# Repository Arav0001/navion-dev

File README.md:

# NAVION - navion-dev
NAVION is a thrust-vector-controlled rocket accompanied by a custom two-board flight computer I designed, built, and flew.

## Results
NAVION's maiden flight reached a ~47 m apogee. The active TVC control loop tracked pitch & yaw through boost and was able to correct 4.5° of yaw error before losing control due to overwhelming pitch error and low motor power, after which the vehicle coasted and descended under parachute to a detected touchdown.
 
### Flight profile
Altitude, vertical velocity, and vertical acceleration across boost, descent, and touchdown, reconstructed from onboard sensor data, see [maiden flight data](FlightData/NAVION-1_DATA.csv):

### TVC response
Tracked gimbal deflection (X/Y) for pitch & yaw during the boost phase, up to TVC lockout at burnout:

## Hardware
 
### Flight computer
Two-board avionics stack: an STM32F4 control board and STM32F2 navigation board communicating over UART DMA, carrying a 9-axis IMU, barometer, GNSS receiver, SPI flash, and µSD storage.

### TVC gimbal
3D-printed 2-axis gimbal actuating the solid rocket motor with ±5° of pitch/yaw deflection, driven by two digital servos:

## Test footage
*TVC gimbal actuating in response to real-time orientation changes of the flight computer*
<video src="https://github.com/user-attachments/assets/a1468e4f-2fa1-48d4-a81f-83034c1c49a3" controls></video>

*Ground test of the black-powder parachute ejection system.*
<video src="https://github.com/user-attachments/assets/dc627b79-1247-45d9-82b1-cf85502bb5d8" controls></video>

## What's in this repo
- [`Code/`](https://github.com/Arav0001/navion-dev/tree/main/Code) - All the firmware for the flight computer.
    - [`CNTRL/`](https://github.com/Arav0001/navion-dev/tree/main/Code/CNTRL) - Firmware for the control (CNTRL) board, targeting the STM32F405RG (STM32CubeIDE Project).
	- [`NAVIG/`](https://github.com/Arav0001/navion-dev/tree/main/Code/NAVIG) - Firmware for the navigation (NAVIG) board, targeting the STM32F205RG (STM32CubeIDE Project).
	- [`CNTRL ESP32/`](https://github.com/Arav0001/navion-dev/tree/main/Code/CNTRL%20ESP32) - Firmware for the [Adafruit HUZZAH32 ESP32](https://www.adafruit.com/product/3405) that runs a webserver for launch control (PlatformIO Project). Contains launch control webserver assets in `data/`.
	- [`NAVION Ground Control/`](https://github.com/Arav0001/navion-dev/tree/main/Code/NAVION%20Ground%20Control) - Firmware for WIP (Work in progress, not currently used or working) ground control radio running off a [Adafruit Feather RFM95W](https://www.adafruit.com/product/3178) (PlatformIO Project).
- [`Designs/`](https://github.com/Arav0001/navion-dev/tree/main/Designs) - OpenRocket designs and simulations for the rocket.
- [`Schematics/`](https://github.com/Arav0001/navion-dev/tree/main/Schematics) - KiCad schematics and PCB files for the flight computer boards.
- [`FlightData/`](https://github.com/Arav0001/navion-dev/tree/main/FlightData) - CSV flight data (only maiden flight as of now)

## Credits
- [FatFS](https://elm-chan.org/fsw/ff/) -> [driver I used](https://github.com/eziya/STM32_SPI_SDCARD)
- [lbthomsen’s W25QXX Driver](https://github.com/lbthomsen/stm32-w25qxx)
- [Sebastian Magdwick’s AHRS Filter](https://x-io.co.uk/open-source-imu-and-ahrs-algorithms/)
- [Adafruit BMP390 Calibration Routine](https://github.com/adafruit/Adafruit_BMP3XX)
- [Chart.js](https://github.com/chartjs/Chart.js)

## Acknowledgements
Thank you to Cory Russell and Merrick Ryman at Birket Engineering for providing guidance and teaching me the skills I needed to make this project happen!

## Inspiration
This project drew inspiration from [Joe Barnard's Scout rocket](https://youtu.be/SH3lR2GLgT0) over at [BPS.space](https://BPS.space). Go check him out!

## Contact
Feel free to contact me at <arav.sonawane@gatech.edu>

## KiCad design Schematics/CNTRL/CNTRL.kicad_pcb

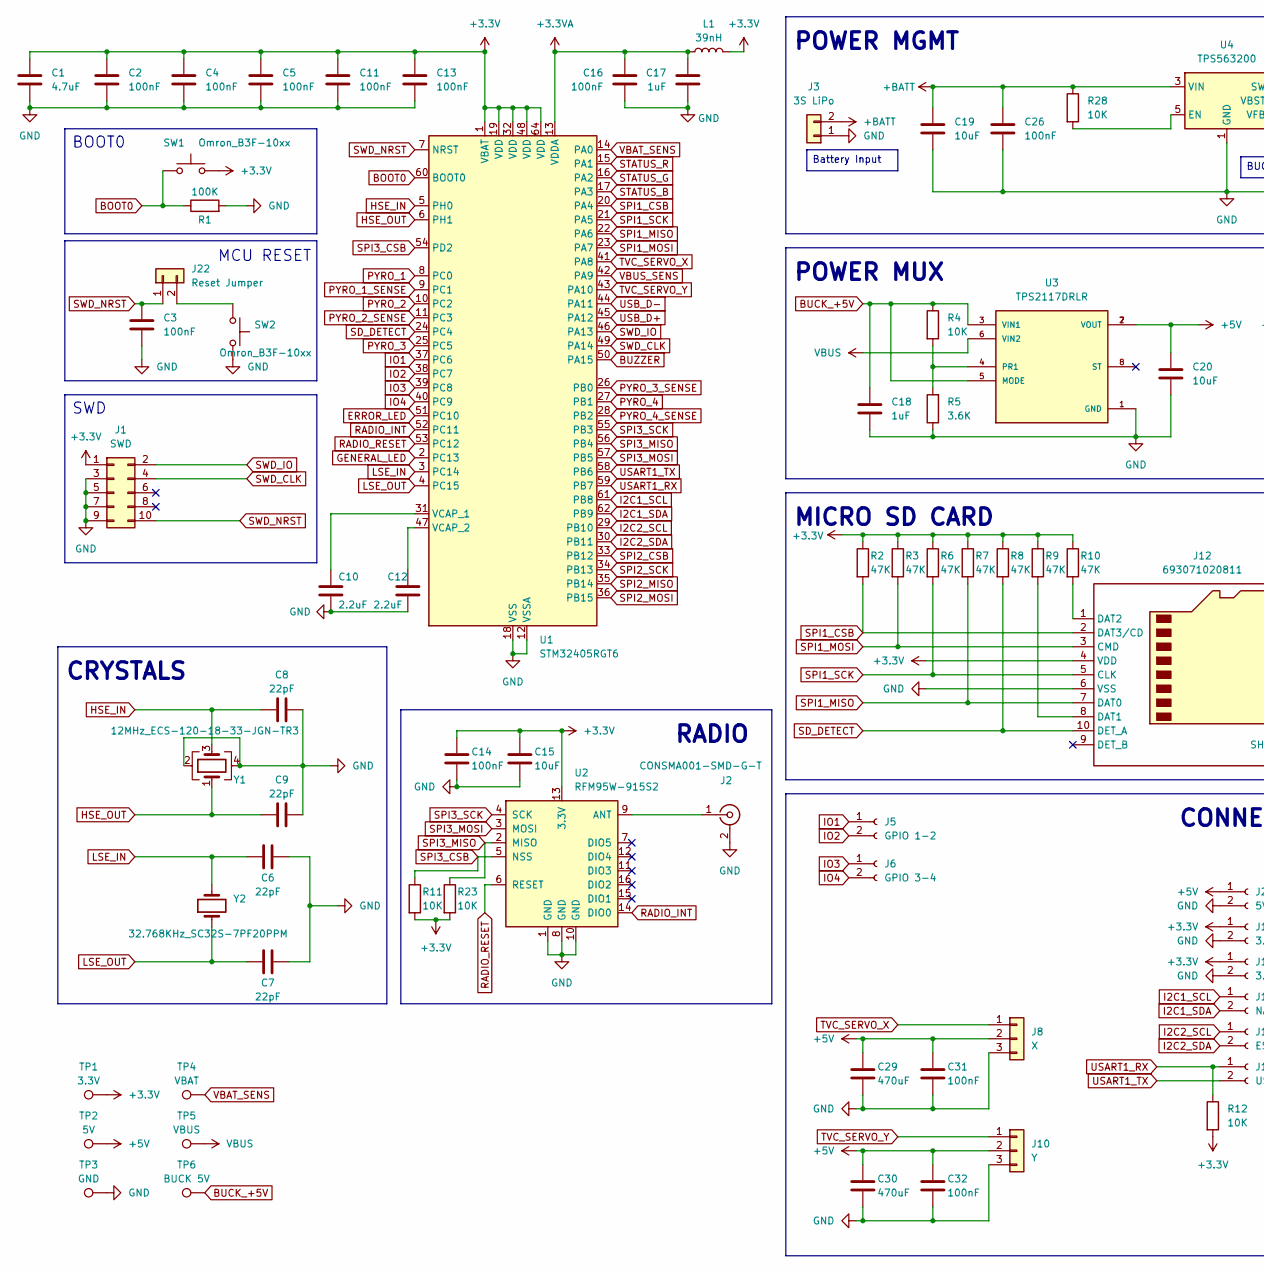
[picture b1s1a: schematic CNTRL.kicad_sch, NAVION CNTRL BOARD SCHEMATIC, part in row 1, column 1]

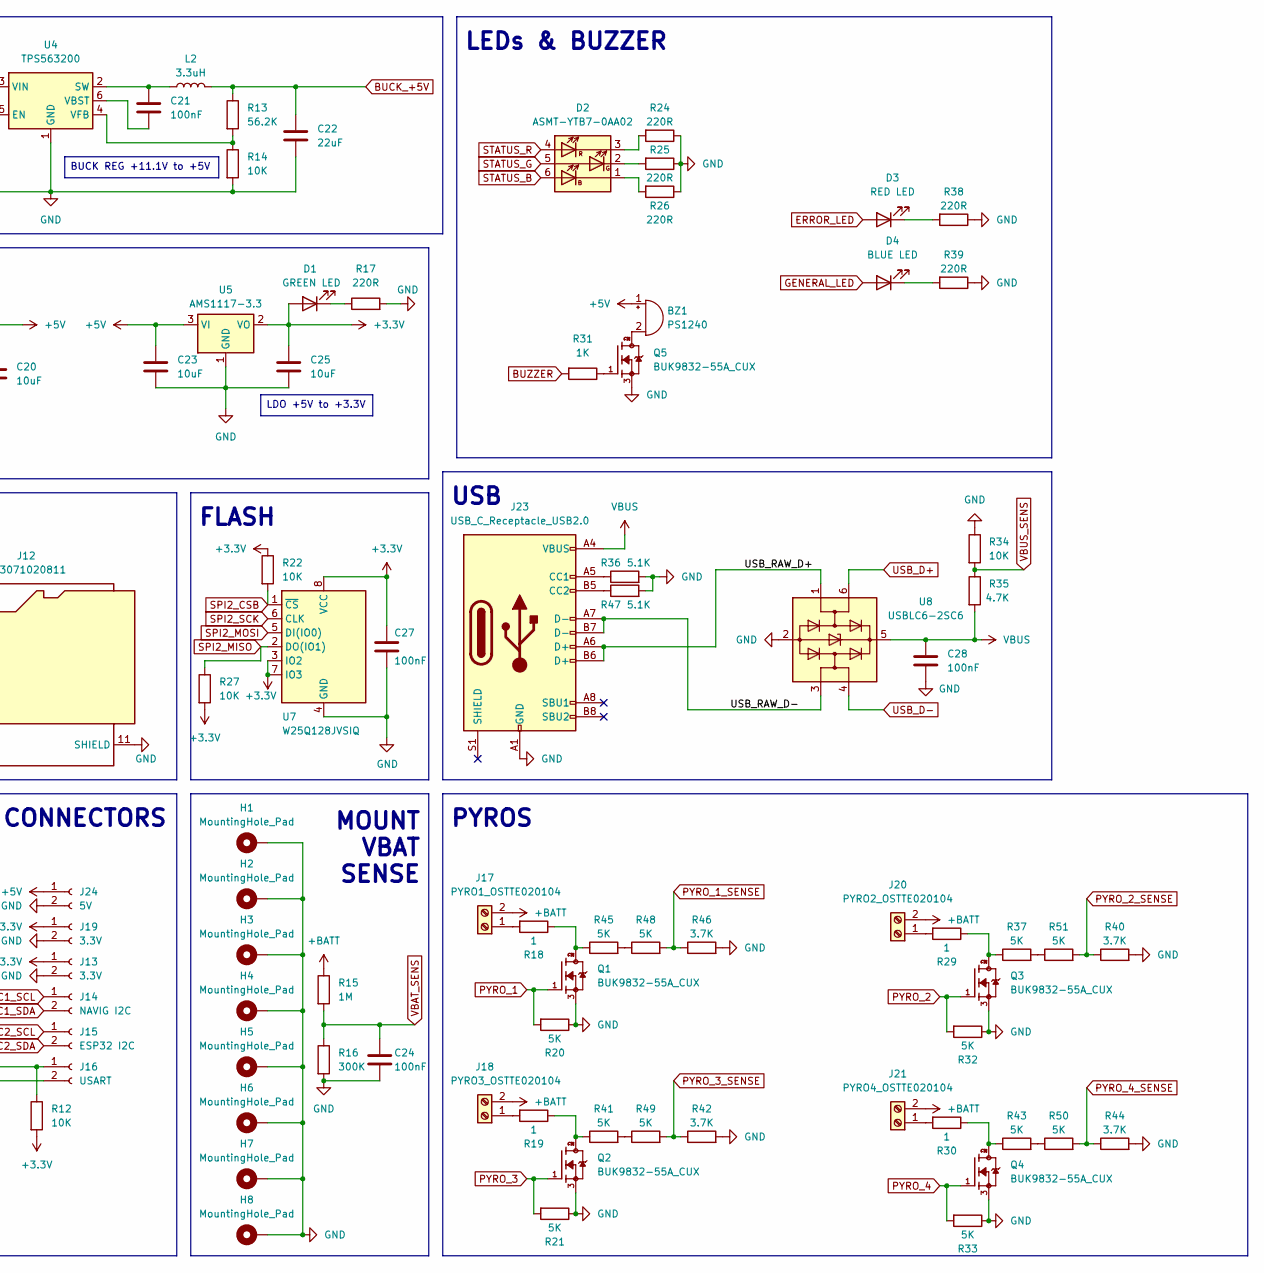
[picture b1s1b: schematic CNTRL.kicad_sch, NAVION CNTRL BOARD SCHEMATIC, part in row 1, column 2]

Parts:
BZ1: PS1240; Buzzer_TDK_PS1240P02BT_D12.2mm_H6.5mm
C1: 4.7uF; C_0603_1608Metric
C2, C3, C4, C5, C11, C13, C14, C16, C21, C24, C26, C27, C28, C31, C32: 100nF; C_0603_1608Metric
C6, C7, C8, C9: 22pF; C_0603_1608Metric
C10, C12: 2.2uF; C_0603_1608Metric
C15, C19, C20, C23, C25: 10uF; C_0603_1608Metric
C17, C18: 1uF; C_0603_1608Metric
C22: 22uF; C_0603_1608Metric
C29, C30: 470uF; CP_Radial_D6.3mm_P2.50mm
D1: GREEN LED; LED_0603_1608Metric
D2: ASMT-YTB7-0AA02; LED_Avago_PLCC6_3x2.8mm
D3: RED LED; LED_0603_1608Metric
D4: BLUE LED; LED_0603_1608Metric
H1, H2, H3, H4, H5, H6, H7, H8: MountingHole_Pad; MountingHole_2.2mm_M2_Pad_TopBottom
J1: SWD; PinHeader_2x05_P1.27mm_Vertical_SMD
J2: CONSMA001-SMD-G-T; LINX_CONSMA001-SMD-G-T
J3: 3S LiPo; AMASS_XT30UPB-M_1x02_P5.0mm_Vertical
J5: GPIO 1-2; TerminalBlock_Phoenix_MPT-0,5-2-2.54_1x02_P2.54mm_Horizontal
J6: GPIO 3-4; TerminalBlock_Phoenix_MPT-0,5-2-2.54_1x02_P2.54mm_Horizontal
J8: X; TerminalBlock_Phoenix_MPT-0,5-3-2.54_1x03_P2.54mm_Horizontal
J10: Y; TerminalBlock_Phoenix_MPT-0,5-3-2.54_1x03_P2.54mm_Horizontal
J12: 693071020811
J13, J19: 3.3V; JST_XH_B2B-XH-A_1x02_P2.50mm_Vertical
J14: NAVIG I2C; JST_XH_B2B-XH-A_1x02_P2.50mm_Vertical
J15: ESP32 I2C; JST_XH_B2B-XH-A_1x02_P2.50mm_Vertical
J16: USART; JST_XH_B2B-XH-A_1x02_P2.50mm_Vertical
J17: PYRO1_OSTTE020104; TerminalBlock_4Ucon_1x02_P3.50mm_Vertical
J18: PYRO3_OSTTE020104; TerminalBlock_4Ucon_1x02_P3.50mm_Vertical
J20: PYRO2_OSTTE020104; TerminalBlock_4Ucon_1x02_P3.50mm_Vertical
J21: PYRO4_OSTTE020104; TerminalBlock_4Ucon_1x02_P3.50mm_Vertical
J22: Reset Jumper; PinHeader_1x02_P2.54mm_Vertical
J23: USB_C_Receptacle_USB2.0; USB_C_Receptacle_GCT_USB4105-xx-A_16P_TopMnt_Horizontal
J24: 5V; JST_XH_B2B-XH-A_1x02_P2.50mm_Vertical
L1: 39nH; L_0603_1608Metric
L2: 3.3uH; L_1210_3225Metric_Pad1.42x2.65mm_HandSolder
Q1, Q2, Q3, Q4, Q5: BUK9832-55A_CUX; TRANS_BUK9832-55A_CUX; PARTREV 02
R1: 100K; R_0603_1608Metric
R2, R3, R6, R7, R8, R9, R10: 47K; R_0603_1608Metric
R4, R11, R12, R14, R22, R23, R27, R28, R34: 10K; R_0603_1608Metric
R5: 3.6K; R_0603_1608Metric
R13: 56.2K; R_0603_1608Metric
R15: 1M; R_0603_1608Metric
R16: 300K; R_0603_1608Metric
R17, R24, R25, R26, R38, R39: 220R; R_0603_1608Metric
R18, R19, R29, R30: 1; R_0603_1608Metric
R20, R21, R32, R33, R37, R41, R43, R45, R48, R49, R50, R51: 5K; R_0603_1608Metric
R31: 1K; R_0603_1608Metric
R35: 4.7K; R_0603_1608Metric
R36, R47: 5.1K; R_0603_1608Metric
R40, R42, R44, R46: 3.7K; R_0603_1608Metric
SW1, SW2: Omron_B3F-10xx; SW_TH_Tactile_Omron_B3F-10xx
TP1: 3.3V; TestPoint_Pad_D2.0mm
TP2: 5V; TestPoint_Pad_D2.0mm
TP3: GND; TestPoint_Pad_D2.0mm
TP4: VBAT; TestPoint_Pad_D2.0mm
TP5: VBUS; TestPoint_Pad_D2.0mm
TP6: BUCK 5V; TestPoint_Pad_D2.0mm
U1: STM32405RGT6; LQFP-64_10x10mm_P0.5mm
U2: RFM95W-915S2; HOPERF_RFM9XW_SMD
U3: TPS2117DRLR; SOT-583-8; PARTREV A
U4: TPS563200; SOT-23-6
U5: AMS1117-3.3; SOT-223-3_TabPin2
U7: W25Q128JVSIQ; SOIC-8_5.3x5.3mm_P1.27mm
U8: USBLC6-2SC6; SOT-23-6
Y1: 12MHz_ECS-120-18-33-JGN-TR3; Crystal_SMD_3225-4Pin_3.2x2.5mm
Y2: 32.768KHz_SC32S-7PF20PPM; Crystal_SMD_3215-2Pin_3.2x1.5mm

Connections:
+3.3V: C1.1, C2.1, C4.1, C5.1, C11.1, C13.1, C14.2, C15.2, C25.1, C27.1, D1.2 (A), J1.1, J12.4 (VDD), J13.1, J19.1, L1.1, R2.1, R3.1, R6.1, R7.1, R8.1, R9.1, R10.1, R11.2, R12.2, R22.1, R23.2, R27.2, SW1.2, TP1.1, U1.1 (VBAT), U1.19 (VDD), U1.32 (VDD), U1.48 (VDD), U1.64 (VDD), U2.13 (3.3V), U5.2 (VO), U7.3 (IO2), U7.7 (IO3), U7.8 (VCC)
+3.3VA: C16.1, C17.1, L1.2, U1.13 (VDDA)
+5V: BZ1.1 (-), C20.1, C23.1, C29.2, C30.2, C31.2, C32.2, J8.2, J10.2, J24.1, TP2.1, U3.2 (VOUT), U3.7 (VOUT), U5.3 (VI)
+BATT: C19.1, C26.1, J3.2, J17.2, J18.2, J20.2, J21.2, R15.1, R28.1, U4.3 (VIN)
/USB_RAW_D+: J23.A6 (D+), J23.B6 (D+), U8.1 (I/O1)
/USB_RAW_D-: J23.A7 (D-), J23.B7 (D-), U8.3 (I/O2)
BOOT0: R1.1, SW1.1, U1.60 (BOOT0)
BUCK_+5V: C18.1, C22.1, L2.2, R4.1, R13.1, TP6.1, U3.3 (VIN1), U3.5 (MODE)
BUZZER: R31.2, U1.50 (PA15)
ERROR_LED: D3.2 (A), U1.51 (PC10)
GENERAL_LED: D4.2 (A), U1.2 (PC13)
GND: C1.2, C2.2, C3.2, C4.2, C5.2, C6.2, C7.2, C8.1, C9.2, C10.1, C11.2, C12.1, C13.2, C14.1, C15.1, C16.2, C17.2, C18.2, C19.2, C20.2, C22.2, C23.2, C24.1, C25.2, C26.2, C27.2, C28.2, C29.1, C30.1, C31.1, C32.1, H1.1, H2.1, H3.1, H4.1, H5.1, H6.1, H7.1, H8.1, J1.3, J1.5, J1.7, J1.9, J2.2 (Ext), J3.1, J8.3, J10.3, J12.6 (VSS), J12.11 (SHIELD), J13.2, J19.2, J23.A1 (GND), J23.A12 (GND), J23.B1 (GND), J23.B12 (GND), J24.2, Q1.3, Q2.3, Q3.3, Q4.3, Q5.3, R1.2, R5.1, R14.2, R16.2, R17.2, R20.1, R21.1, R24.1, R25.1, R26.1, R32.1, R33.1, R34.1, R36.2, R38.1, R39.1, R40.2, R42.2, R44.2, R46.2, R47.2, SW2.2, TP3.1, U1.12 (VSSA), U1.18 (VSS), U1.63 (VSS), U2.1 (GND), U2.8 (GND), U2.10 (GND), U3.1 (GND), U4.1 (GND), U5.1 (GND), U7.4 (GND), U8.2 (GND), Y1.2, Y1.4
HSE_IN: C8.2, U1.5 (PH0), Y1.3
HSE_OUT: C9.1, U1.6 (PH1), Y1.1
I2C1_SCL: J14.1, U1.61 (PB8)
I2C1_SDA: J14.2, U1.62 (PB9)
I2C2_SCL: J15.1, U1.29 (PB10)
I2C2_SDA: J15.2, U1.30 (PB11)
IO1: J5.1, U1.37 (PC6)
IO2: J5.2, U1.38 (PC7)
IO3: J6.1, U1.39 (PC8)
IO4: J6.2, U1.40 (PC9)
LSE_IN: C6.1, U1.3 (PC14), Y2.2
LSE_OUT: C7.1, U1.4 (PC15), Y2.1
unnamed: BZ1.2 (+), Q5.2, Q5.4
unnamed: D1.1 (K), R17.1
unnamed: D2.1 (KB), R26.2
unnamed: D2.2 (KG), R25.2
unnamed: D2.3 (KR), R24.2
unnamed: D3.1 (K), R38.2
unnamed: D4.1 (K), R39.2
unnamed: J2.1 (In), U2.9 (ANT)
unnamed: J12.8 (DAT1), R9.2
unnamed: J12.1 (DAT2), R10.2
unnamed: J17.1, R18.2
unnamed: J18.1, R19.2
unnamed: J20.1, R29.2
unnamed: J21.1, R30.2
unnamed: J22.2, SW2.1
unnamed: J23.A5 (CC1), R36.1
unnamed: J23.B5 (CC2), R47.1
unnamed: Q1.2, Q1.4, R18.1, R45.1
unnamed: Q2.2, Q2.4, R19.1, R41.1
unnamed: Q3.2, Q3.4, R29.1, R37.1
unnamed: Q4.2, Q4.4, R30.1, R43.1
unnamed: Q5.1, R31.1
unnamed: R37.2, R51.1
unnamed: R41.2, R49.1
unnamed: R43.2, R50.1
unnamed: R45.2, R48.1
unnamed: C10.2, U1.31 (VCAP_1)
unnamed: C12.2, U1.47 (VCAP_2)
unnamed: R4.2, R5.2, U3.4 (PR1)
unnamed: R28.2, U4.5 (EN)
unnamed: C21.1, L2.1, U4.2 (SW)
unnamed: C21.2, U4.6 (VBST)
unnamed: R13.2, R14.1, U4.4 (VFB)
PYRO_1: Q1.1, R20.2, U1.8 (PC0)
PYRO_1_SENSE: R46.1, R48.2, U1.9 (PC1)
PYRO_2: Q3.1, R32.2, U1.10 (PC2)
PYRO_2_SENSE: R40.1, R51.2, U1.11 (PC3)
PYRO_3: Q2.1, R21.2, U1.25 (PC5)
PYRO_3_SENSE: R42.1, R49.2, U1.26 (PB0)
PYRO_4: Q4.1, R33.2, U1.27 (PB1)
PYRO_4_SENSE: R44.1, R50.2, U1.28 (PB2)
RADIO_INT: U1.52 (PC11), U2.14 (DIO0)
RADIO_RESET: U1.53 (PC12), U2.6 (RESET)
SD_DETECT: J12.10 (DET_A), R8.2, U1.24 (PC4)
SPI1_CSB: J12.2 (DAT3/CD), R2.2, U1.20 (PA4)
SPI1_MISO: J12.7 (DAT0), R7.2, U1.22 (PA6)
SPI1_MOSI: J12.3 (CMD), R3.2, U1.23 (PA7)
SPI1_SCK: J12.5 (CLK), R6.2, U1.21 (PA5)
SPI2_CSB: R22.2, U1.33 (PB12), U7.1 (~CS)
SPI2_MISO: R27.1, U1.35 (PB14), U7.2 (DO(IO1))
SPI2_MOSI: U1.36 (PB15), U7.5 (DI(IO0))
SPI2_SCK: U1.34 (PB13), U7.6 (CLK)
SPI3_CSB: R11.1, U1.54 (PD2), U2.5 (NSS)
SPI3_MISO: R23.1, U1.56 (PB4), U2.2 (MISO)
SPI3_MOSI: U1.57 (PB5), U2.3 (MOSI)
SPI3_SCK: U1.55 (PB3), U2.4 (SCK)
STATUS_B: D2.6 (AB), U1.17 (PA3)
STATUS_G: D2.5 (AG), U1.16 (PA2)
STATUS_R: D2.4 (AR), U1.15 (PA1)
SWD_CLK: J1.4, U1.49 (PA14)
SWD_IO: J1.2, U1.46 (PA13)
SWD_NRST: C3.1, J1.10, J22.1, U1.7 (NRST)
TVC_SERVO_X: J8.1, U1.41 (PA8)
TVC_SERVO_Y: J10.1, U1.43 (PA10)
USART1_RX: J16.1, R12.1, U1.59 (PB7)
USART1_TX: J16.2, U1.58 (PB6)
USB_D+: U1.45 (PA12), U8.6 (I/O1)
USB_D-: U1.44 (PA11), U8.4 (I/O2)
VBAT_SENS: C24.2, R15.2, R16.1, TP4.1, U1.14 (PA0)
VBUS: C28.1, J23.A4 (VBUS), J23.A9 (VBUS), J23.B4 (VBUS), J23.B9 (VBUS), R35.2, TP5.1, U3.6 (VIN2), U8.5 (VBUS)
VBUS_SENS: R34.2, R35.1, U1.42 (PA9)

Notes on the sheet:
CONNECTORS
PYROS
BOOT0
POWER MUX
SWD
FLASH
LEDs & BUZZER
MCU RESET
MOUNT VBAT SENSE
CRYSTALS
MICRO SD CARD
POWER MGMT
RADIO
USB
Battery Input
LDO +5V to +3.3V
BUCK REG +11.1V to +5V

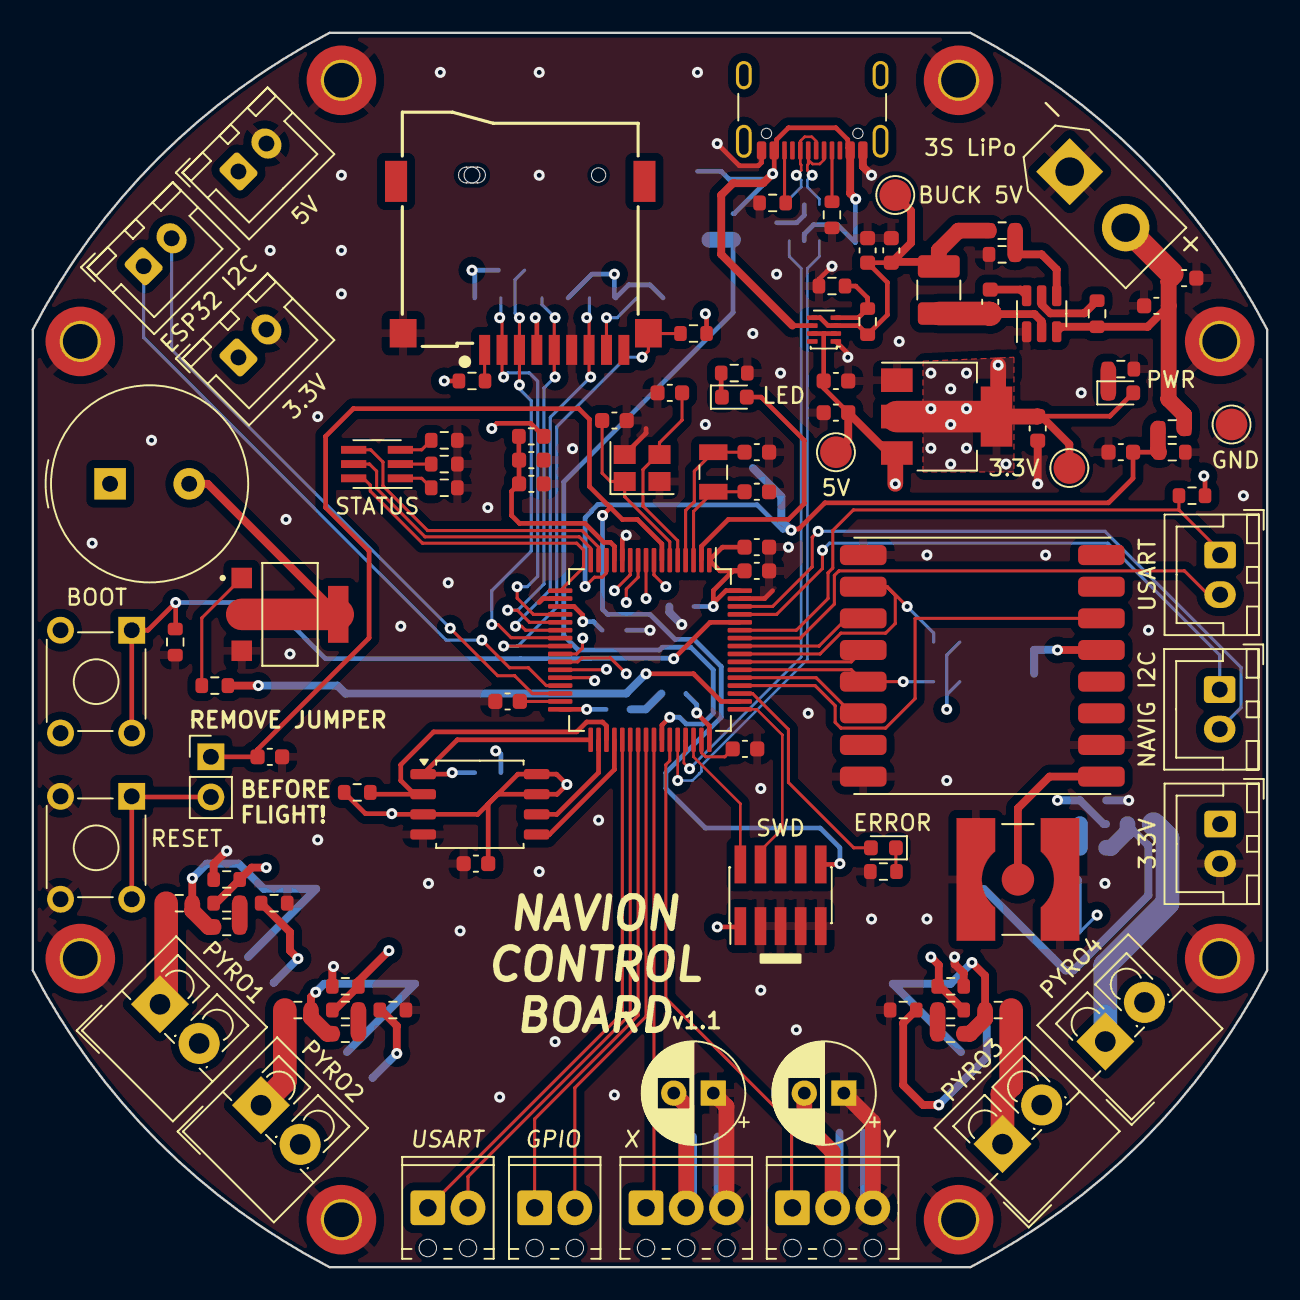
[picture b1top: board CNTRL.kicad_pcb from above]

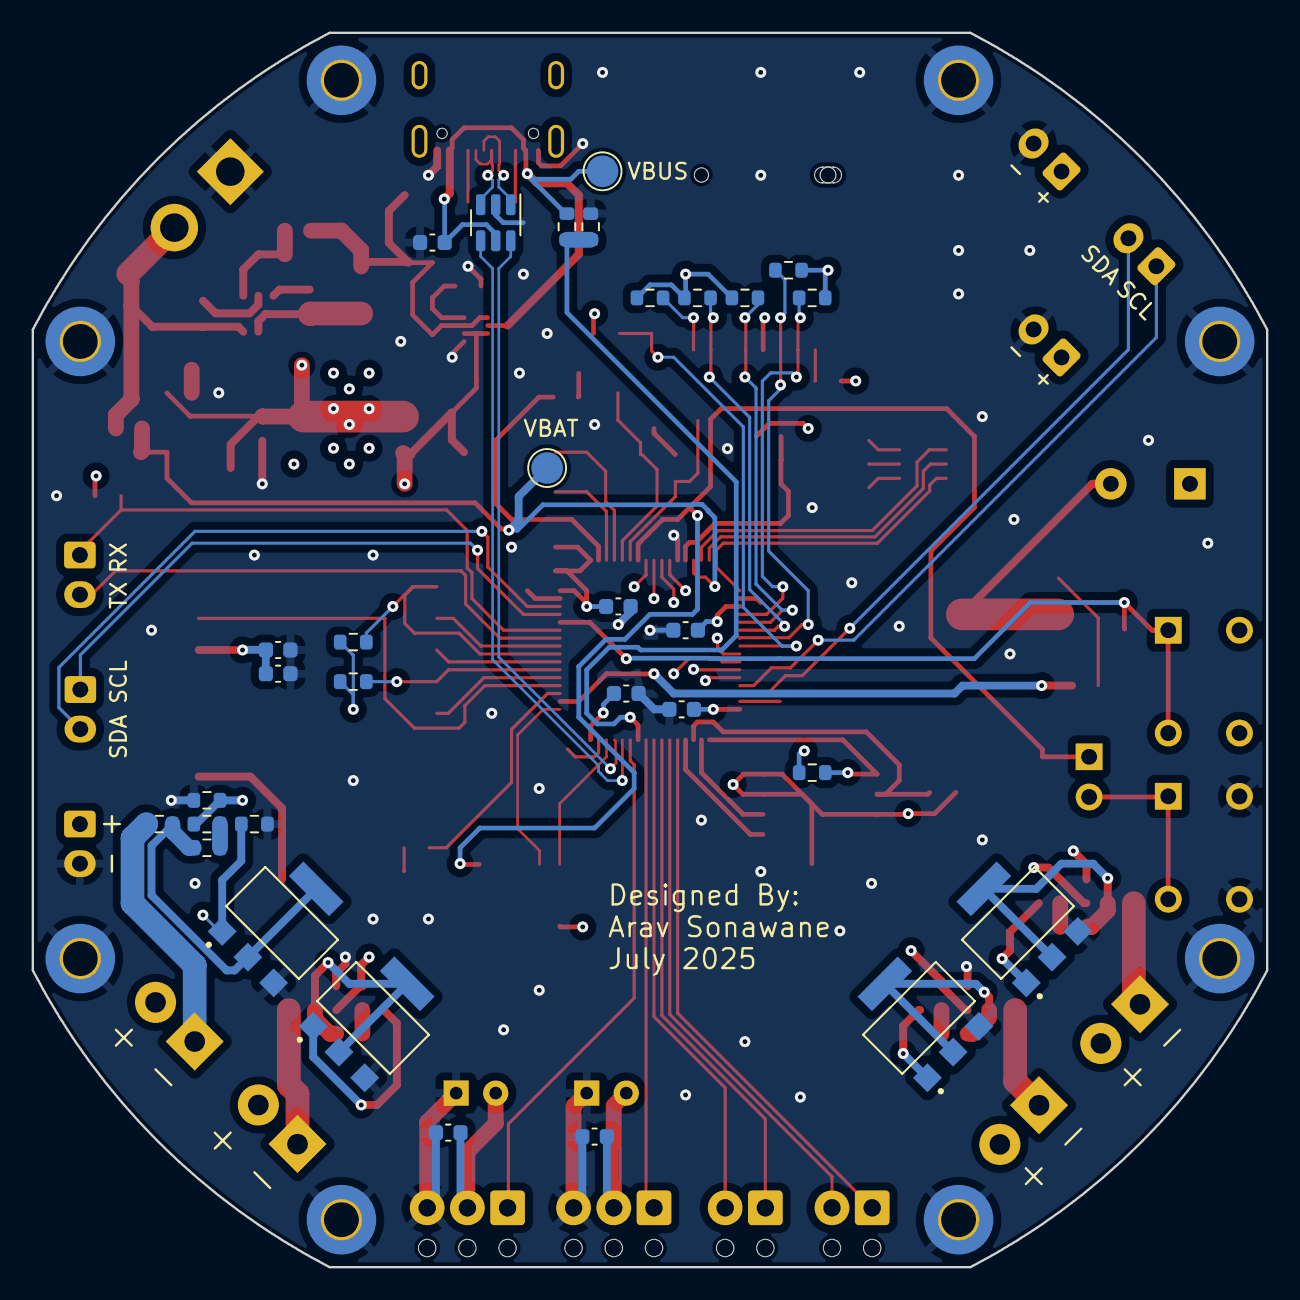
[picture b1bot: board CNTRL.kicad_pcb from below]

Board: 4 copper layers, 78.0 x 78.0 mm, 140 parts (31 on the bottom side), 95 nets.

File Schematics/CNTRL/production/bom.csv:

Designator,Footprint,Quantity,Value,LCSC Part #
BZ1,Buzzer_TDK_PS1240P02BT_D12.2mm_H6.5mm,1,PS1240,
C1,0603,1,4.7uF,
"C10, C12",0603,2,2.2uF,
"C11, C13, C14, C16, C2, C21, C24, C26, C27, C28, C3, C31, C32, C4, C5",0603,15,100nF,
"C15, C19, C20, C23, C25",0603,5,10uF,
"C17, C18",0603,2,1uF,
C22,0603,1,22uF,
"C29, C30",CP_Radial_D6.3mm_P2.50mm,2,470uF,
"C6, C7, C8, C9",0603,4,22pF,
D1,0603,1,GREEN LED,
D2,LED_Avago_PLCC6_3x2.8mm,1,ASMT-YTB7-0AA02,
D3,0603,1,RED LED,
D4,0603,1,BLUE LED,
"H1, H2, H3, H4, H5, H6, H7, H8",MountingHole_2.2mm_M2_Pad_TopBottom,8,MountingHole_Pad,
J1,PinHeader_2x05_P1.27mm_Vertical_SMD,1,SWD,
J10,"TerminalBlock_Phoenix_MPT-0,5-3-2.54_1x03_P2.54mm_Horizontal",1,Y,
J12,693071020811,1,693071020811,
"J13, J19",JST_XH_B2B-XH-A_1x02_P2.50mm_Vertical,2,3.3V,
J14,JST_XH_B2B-XH-A_1x02_P2.50mm_Vertical,1,NAVIG I2C,
J15,JST_XH_B2B-XH-A_1x02_P2.50mm_Vertical,1,ESP32 I2C,
J16,JST_XH_B2B-XH-A_1x02_P2.50mm_Vertical,1,USART,
J17,TerminalBlock_4Ucon_1x02_P3.50mm_Vertical,1,PYRO1_OSTTE020104,
J18,TerminalBlock_4Ucon_1x02_P3.50mm_Vertical,1,PYRO3_OSTTE020104,
J2,LINX_CONSMA001-SMD-G-T,1,CONSMA001-SMD-G-T,
J20,TerminalBlock_4Ucon_1x02_P3.50mm_Vertical,1,PYRO2_OSTTE020104,
J21,TerminalBlock_4Ucon_1x02_P3.50mm_Vertical,1,PYRO4_OSTTE020104,
J22,PinHeader_1x02_P2.54mm_Vertical,1,Reset Jumper,
J23,USB_C_Receptacle_GCT_USB4105-xx-A_16P_TopMnt_Horizontal,1,USB_C_Receptacle_USB2.0,
J24,JST_XH_B2B-XH-A_1x02_P2.50mm_Vertical,1,5V,
J3,AMASS_XT30UPB-M_1x02_P5.0mm_Vertical,1,3S LiPo,
J5,"TerminalBlock_Phoenix_MPT-0,5-2-2.54_1x02_P2.54mm_Horizontal",1,GPIO 1-2,
J6,"TerminalBlock_Phoenix_MPT-0,5-2-2.54_1x02_P2.54mm_Horizontal",1,GPIO 3-4,
J8,"TerminalBlock_Phoenix_MPT-0,5-3-2.54_1x03_P2.54mm_Horizontal",1,X,
L1,0603,1,39nH,
L2,1210,1,3.3uH,
"Q1, Q2, Q3, Q4, Q5",TRANS_BUK9832-55A_CUX,5,BUK9832-55A_CUX,
R1,0603,1,100K,
"R10, R2, R3, R6, R7, R8, R9",0603,7,47K,
"R11, R12, R14, R22, R23, R27, R28, R34, R4",0603,9,10K,
R13,0603,1,56.2K,
R15,0603,1,1M,
R16,0603,1,300K,
"R17, R24, R25, R26, R38, R39",0603,6,220R,
"R18, R19, R29, R30",0603,4,1,
"R20, R21, R32, R33, R37, R41, R43, R45, R48, R49, R50, R51",0603,12,5K,
R31,0603,1,1K,
R35,0603,1,4.7K,
"R36, R47",0603,2,5.1K,
"R40, R42, R44, R46",0603,4,3.7K,
R5,0603,1,3.6K,
"SW1, SW2",SW_TH_Tactile_Omron_B3F-10xx,2,Omron_B3F-10xx,
TP1,TestPoint_Pad_D2.0mm,1,3.3V,
TP2,TestPoint_Pad_D2.0mm,1,5V,
TP3,TestPoint_Pad_D2.0mm,1,GND,
TP4,TestPoint_Pad_D2.0mm,1,VBAT,
TP5,TestPoint_Pad_D2.0mm,1,VBUS,
TP6,TestPoint_Pad_D2.0mm,1,BUCK 5V,
U1,LQFP-64_10x10mm_P0.5mm,1,STM32405RGT6,
U2,HOPERF_RFM9XW_SMD,1,RFM95W-915S2,
U3,SOT-583-8,1,TPS2117DRLR,
U4,SOT-23-6,1,TPS563200,
U5,SOT-223-3_TabPin2,1,AMS1117-3.3,
U7,SOIC-8_5.3x5.3mm_P1.27mm,1,W25Q128JVSIQ,
U8,SOT-23-6,1,USBLC6-2SC6,
Y1,Crystal_SMD_3225-4Pin_3.2x2.5mm,1,12MHz_ECS-120-18-33-JGN-TR3,
Y2,Crystal_SMD_3215-2Pin_3.2x1.5mm,1,32.768KHz_SC32S-7PF20PPM,

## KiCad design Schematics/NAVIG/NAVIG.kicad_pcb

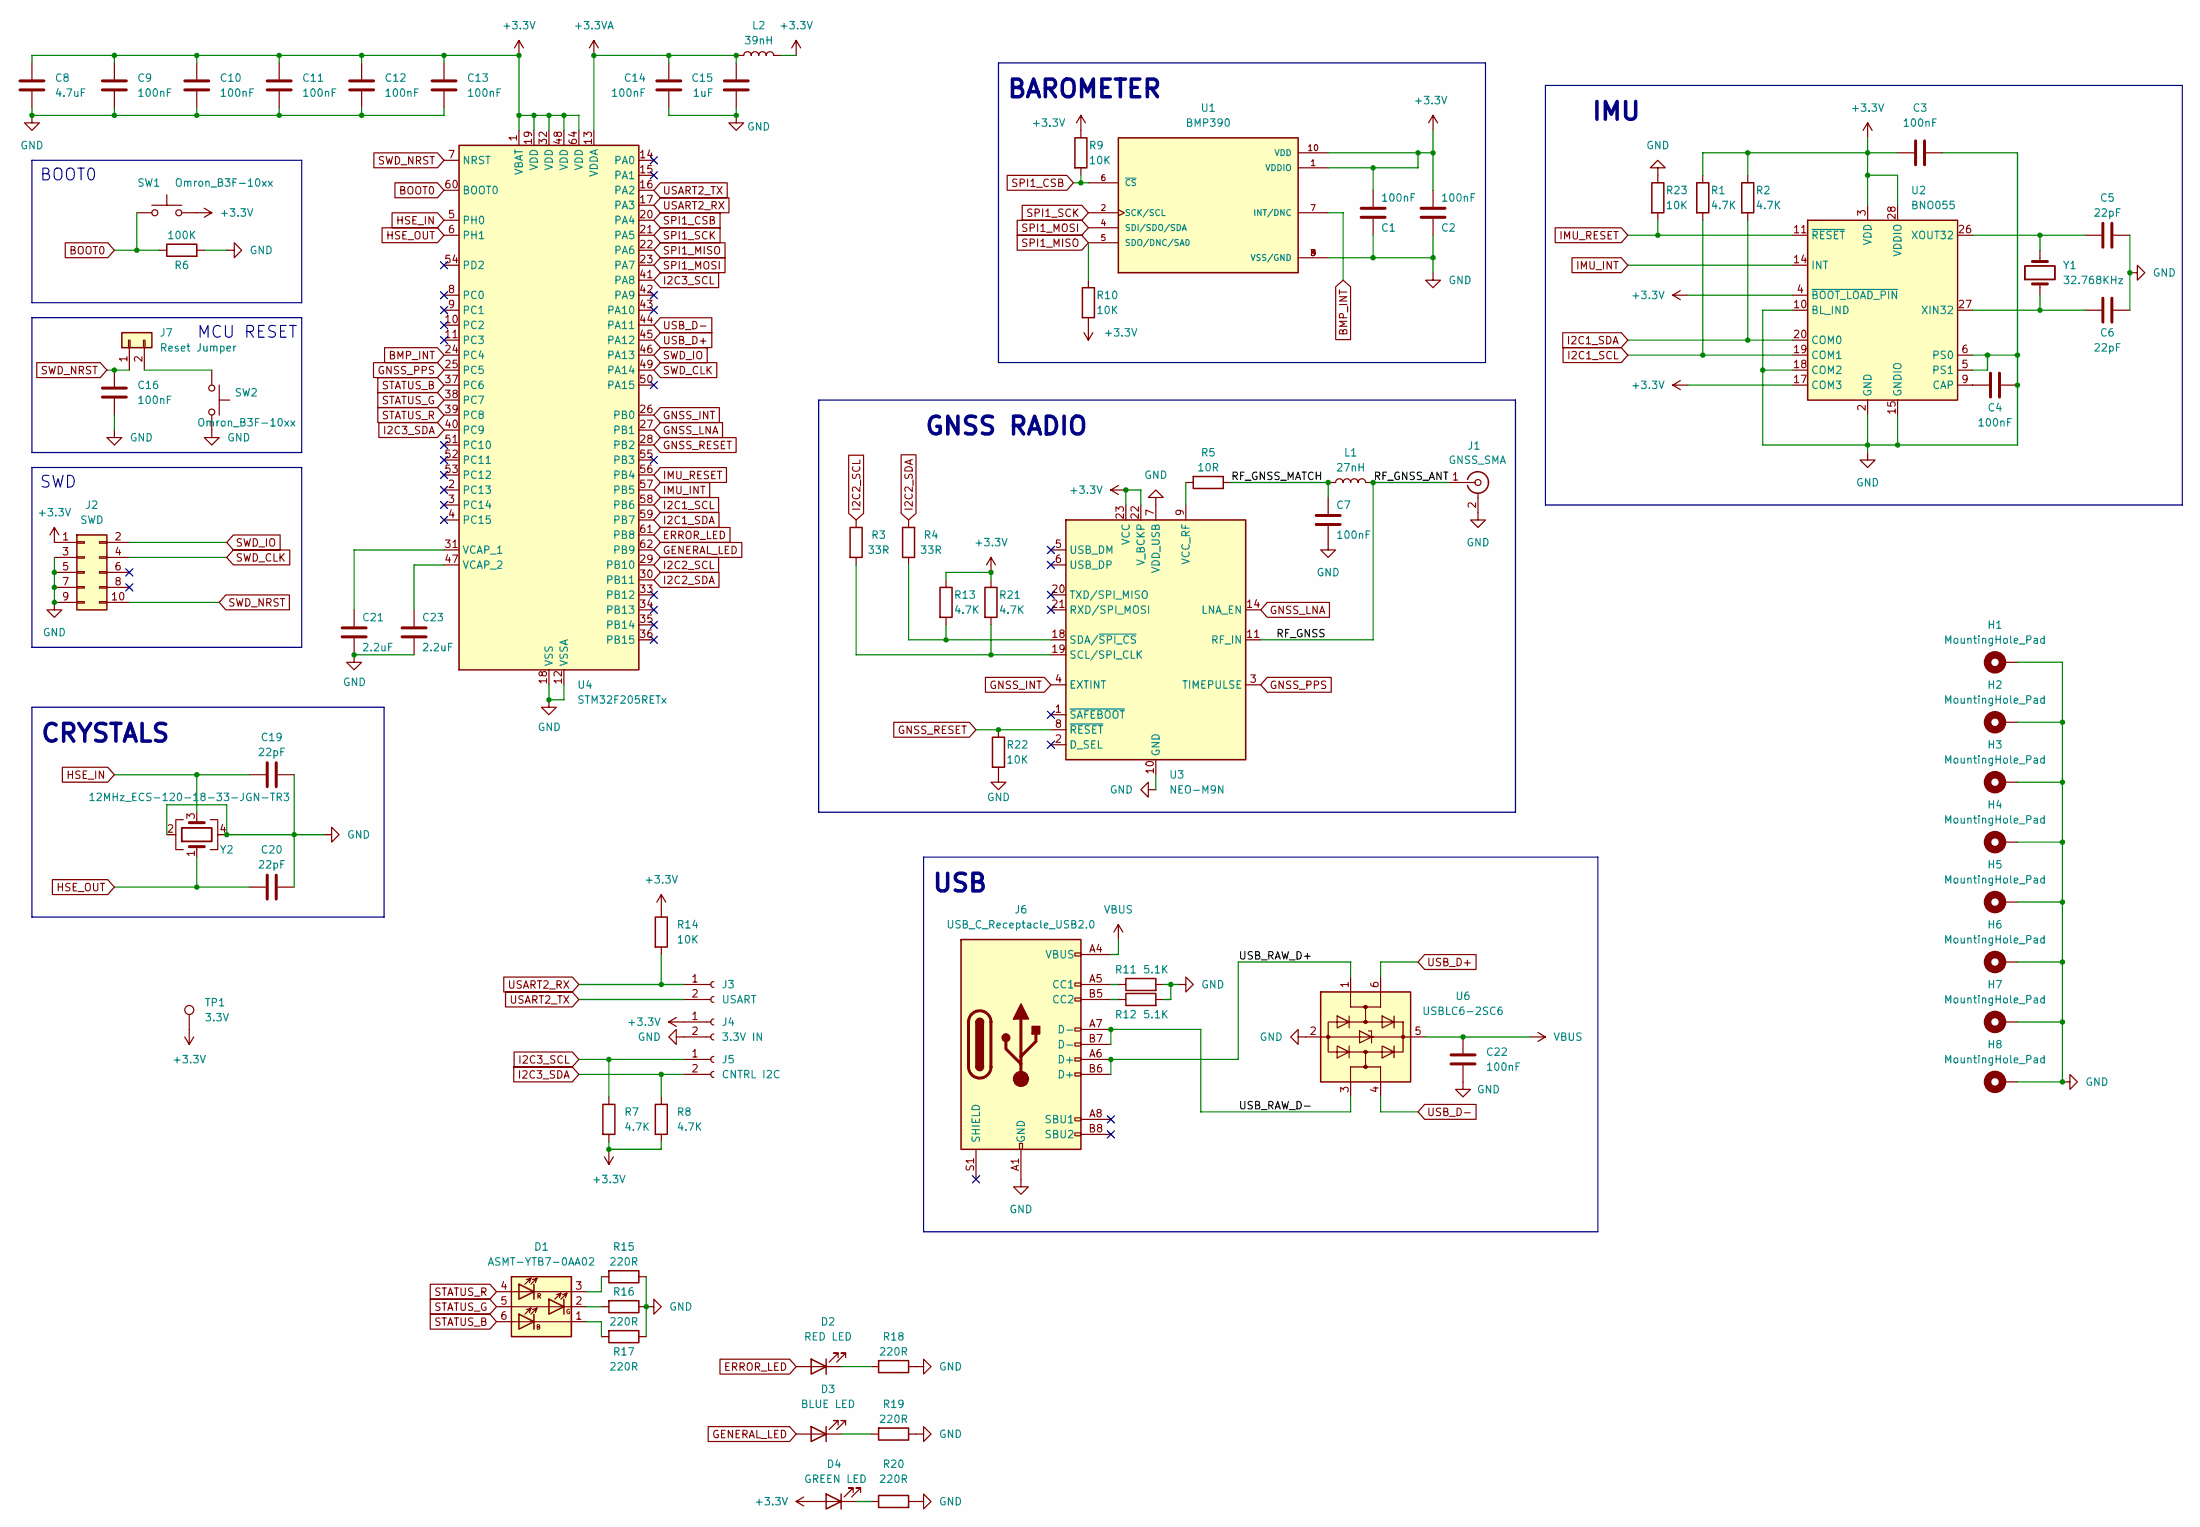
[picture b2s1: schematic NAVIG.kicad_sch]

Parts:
C1, C2, C3, C4, C7, C9, C10, C11, C12, C13, C14, C16, C22: 100nF; C_0603_1608Metric
C5, C6, C19, C20: 22pF; C_0603_1608Metric
C8: 4.7uF; C_0603_1608Metric
C15: 1uF; C_0603_1608Metric
C21, C23: 2.2uF; C_0603_1608Metric
D1: ASMT-YTB7-0AA02; LED_Avago_PLCC6_3x2.8mm
D2: RED LED; LED_0603_1608Metric
D3: BLUE LED; LED_0603_1608Metric
D4: GREEN LED; LED_0603_1608Metric
H1, H2, H3, H4, H5, H6, H7, H8: MountingHole_Pad; MountingHole_2.2mm_M2_Pad_TopBottom
J1: GNSS_SMA; SMA_Amphenol_132134-10_Vertical
J2: SWD; PinHeader_2x05_P1.27mm_Vertical_SMD
J3: USART; JST_XH_B2B-XH-A_1x02_P2.50mm_Vertical
J4: 3.3V IN; JST_XH_B2B-XH-A_1x02_P2.50mm_Vertical
J5: CNTRL I2C; JST_XH_B2B-XH-A_1x02_P2.50mm_Vertical
J6: USB_C_Receptacle_USB2.0; USB_C_Receptacle_GCT_USB4105-xx-A_16P_TopMnt_Horizontal
J7: Reset Jumper; PinHeader_1x02_P2.54mm_Vertical
L1: 27nH; L_TDK_NLV32_3.2x2.5mm
L2: 39nH; L_0603_1608Metric
R1, R2, R7, R8, R13, R21: 4.7K; R_0603_1608Metric
R3, R4: 33R; R_0603_1608Metric
R5: 10R; R_0603_1608Metric
R6: 100K; R_0603_1608Metric
R9, R10, R14, R22, R23: 10K; R_0603_1608Metric
R11, R12: 5.1K; R_0603_1608Metric
R15, R16, R17, R18, R19, R20: 220R; R_0603_1608Metric
SW1, SW2: Omron_B3F-10xx; SW_TH_Tactile_Omron_B3F-10xx
TP1: 3.3V; TestPoint_Pad_D2.0mm
U1: BMP390; XDCR_BMP390L; PARTREV 1.7
U2: BNO055; LGA-28_5.2x3.8mm_P0.5mm
U3: NEO-M9N; ublox_NEO
U4: STM32F205RETx; LQFP-64_10x10mm_P0.5mm
U6: USBLC6-2SC6; SOT-23-6
Y1: 32.768KHz; Crystal_SMD_3215-2Pin_3.2x1.5mm
Y2: 12MHz_ECS-120-18-33-JGN-TR3; Crystal_SMD_3225-4Pin_3.2x2.5mm

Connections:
+3.3V: C1.1, C2.1, C3.2, C8.1, C9.1, C10.1, C11.1, C12.1, C13.1, D4.2 (A), J2.1, J4.1, L2.1, R1.1, R2.1, R7.2, R8.2, R9.1, R10.2, R13.1, R14.1, R21.1, SW1.2, TP1.1, U1.1 (VDDIO), U1.10 (VDD), U2.3 (VDD), U2.4 (~BOOT_LOAD_PIN), U2.17 (COM3), U2.28 (VDDIO), U3.22 (V_BCKP), U3.23 (VCC), U4.1 (VBAT), U4.19 (VDD), U4.32 (VDD), U4.48 (VDD), U4.64 (VDD)
+3.3VA: C14.1, C15.1, L2.2, U4.13 (VDDA)
/RF_GNSS: J1.1 (In), L1.1, U3.11 (RF_IN)
/RF_GNSS_MATCH: C7.1, L1.2, R5.1
/USB_RAW_D+: J6.A6 (D+), J6.B6 (D+), U6.1 (I/O1)
/USB_RAW_D-: J6.A7 (D-), J6.B7 (D-), U6.3 (I/O2)
BMP_INT: U1.7 (INT/DNC), U4.24 (PC4)
BOOT0: R6.1, SW1.1, U4.60 (BOOT0)
ERROR_LED: D2.2 (A), U4.61 (PB8)
GENERAL_LED: D3.2 (A), U4.62 (PB9)
GND: C1.2, C2.2, C3.1, C4.1, C5.2, C6.2, C7.2, C8.2, C9.2, C10.2, C11.2, C12.2, C13.2, C14.2, C15.2, C16.2, C19.1, C20.2, C21.1, C22.2, C23.1, H1.1, H2.1, H3.1, H4.1, H5.1, H6.1, H7.1, H8.1, J1.2 (Ext), J2.3, J2.5, J2.7, J2.9, J4.2, J6.A1 (GND), J6.A12 (GND), J6.B1 (GND), J6.B12 (GND), R6.2, R11.2, R12.2, R15.1, R16.1, R17.1, R18.1, R19.1, R20.2, R22.2, R23.1, SW2.2, U1.3 (VSS/GND), U1.8 (VSS/GND), U1.9 (VSS/GND), U2.2 (GND), U2.5 (PS1), U2.6 (PS0), U2.10 (BL_IND), U2.15 (GNDIO), U2.16 (GNDIO), U2.18 (COM2), U2.25 (GNDIO), U3.7 (VDD_USB), U3.10 (GND), U3.12 (GND), U3.13 (GND), U3.24 (GND), U4.12 (VSSA), U4.18 (VSS), U4.63 (VSS), U6.2 (GND), Y2.2, Y2.4
GNSS_INT: U3.4 (EXTINT), U4.26 (PB0)
GNSS_LNA: U3.14 (LNA_EN), U4.27 (PB1)
GNSS_PPS: U3.3 (TIMEPULSE), U4.25 (PC5)
GNSS_RESET: R22.1, U3.8 (~RESET), U4.28 (PB2)
HSE_IN: C19.2, U4.5 (PH0), Y2.3
HSE_OUT: C20.1, U4.6 (PH1), Y2.1
I2C1_SCL: R1.2, U2.19 (COM1), U4.58 (PB6)
I2C1_SDA: R2.2, U2.20 (COM0), U4.59 (PB7)
I2C2_SCL: R3.1, U4.29 (PB10)
I2C2_SDA: R4.2, U4.30 (PB11)
I2C3_SCL: J5.1, R7.1, U4.41 (PA8)
I2C3_SDA: J5.2, R8.1, U4.40 (PC9)
IMU_INT: U2.14 (INT), U4.57 (PB5)
IMU_RESET: R23.2, U2.11 (~RESET), U4.56 (PB4)
unnamed: D1.1 (KB), R17.2
unnamed: D1.2 (KG), R16.2
unnamed: D1.3 (KR), R15.2
unnamed: D2.1 (K), R18.2
unnamed: D3.1 (K), R19.2
unnamed: D4.1 (K), R20.1
unnamed: J6.A5 (CC1), R11.1
unnamed: J6.B5 (CC2), R12.1
unnamed: J7.2, SW2.1
unnamed: C4.2, U2.9 (CAP)
unnamed: C6.1, U2.27 (XIN32), Y1.1
unnamed: C5.1, U2.26 (XOUT32), Y1.2
unnamed: R3.2, R21.2, U3.19 (SCL/SPI_CLK)
unnamed: R4.1, R13.2, U3.18 (SDA/~SPI_CS)
unnamed: R5.2, U3.9 (VCC_RF)
unnamed: C21.2, U4.31 (VCAP_1)
unnamed: C23.2, U4.47 (VCAP_2)
SPI1_CSB: R9.2, U1.6 (~CS), U4.20 (PA4)
SPI1_MISO: R10.1, U1.5 (SDO/DNC/SA0), U4.22 (PA6)
SPI1_MOSI: U1.4 (SDI/SDO/SDA), U4.23 (PA7)
SPI1_SCK: U1.2 (SCK/SCL), U4.21 (PA5)
STATUS_B: D1.6 (AB), U4.37 (PC6)
STATUS_G: D1.5 (AG), U4.38 (PC7)
STATUS_R: D1.4 (AR), U4.39 (PC8)
SWD_CLK: J2.4, U4.49 (PA14)
SWD_IO: J2.2, U4.46 (PA13)
SWD_NRST: C16.1, J2.10, J7.1, U4.7 (NRST)
USART2_RX: J3.1, R14.2, U4.17 (PA3)
USART2_TX: J3.2, U4.16 (PA2)
USB_D+: U4.45 (PA12), U6.6 (I/O1)
USB_D-: U4.44 (PA11), U6.4 (I/O2)
VBUS: C22.1, J6.A4 (VBUS), J6.A9 (VBUS), J6.B4 (VBUS), J6.B9 (VBUS), U6.5 (VBUS)

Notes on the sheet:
IMU
GNSS RADIO
SWD
USB
CRYSTALS
BOOT0
MCU RESET
BAROMETER

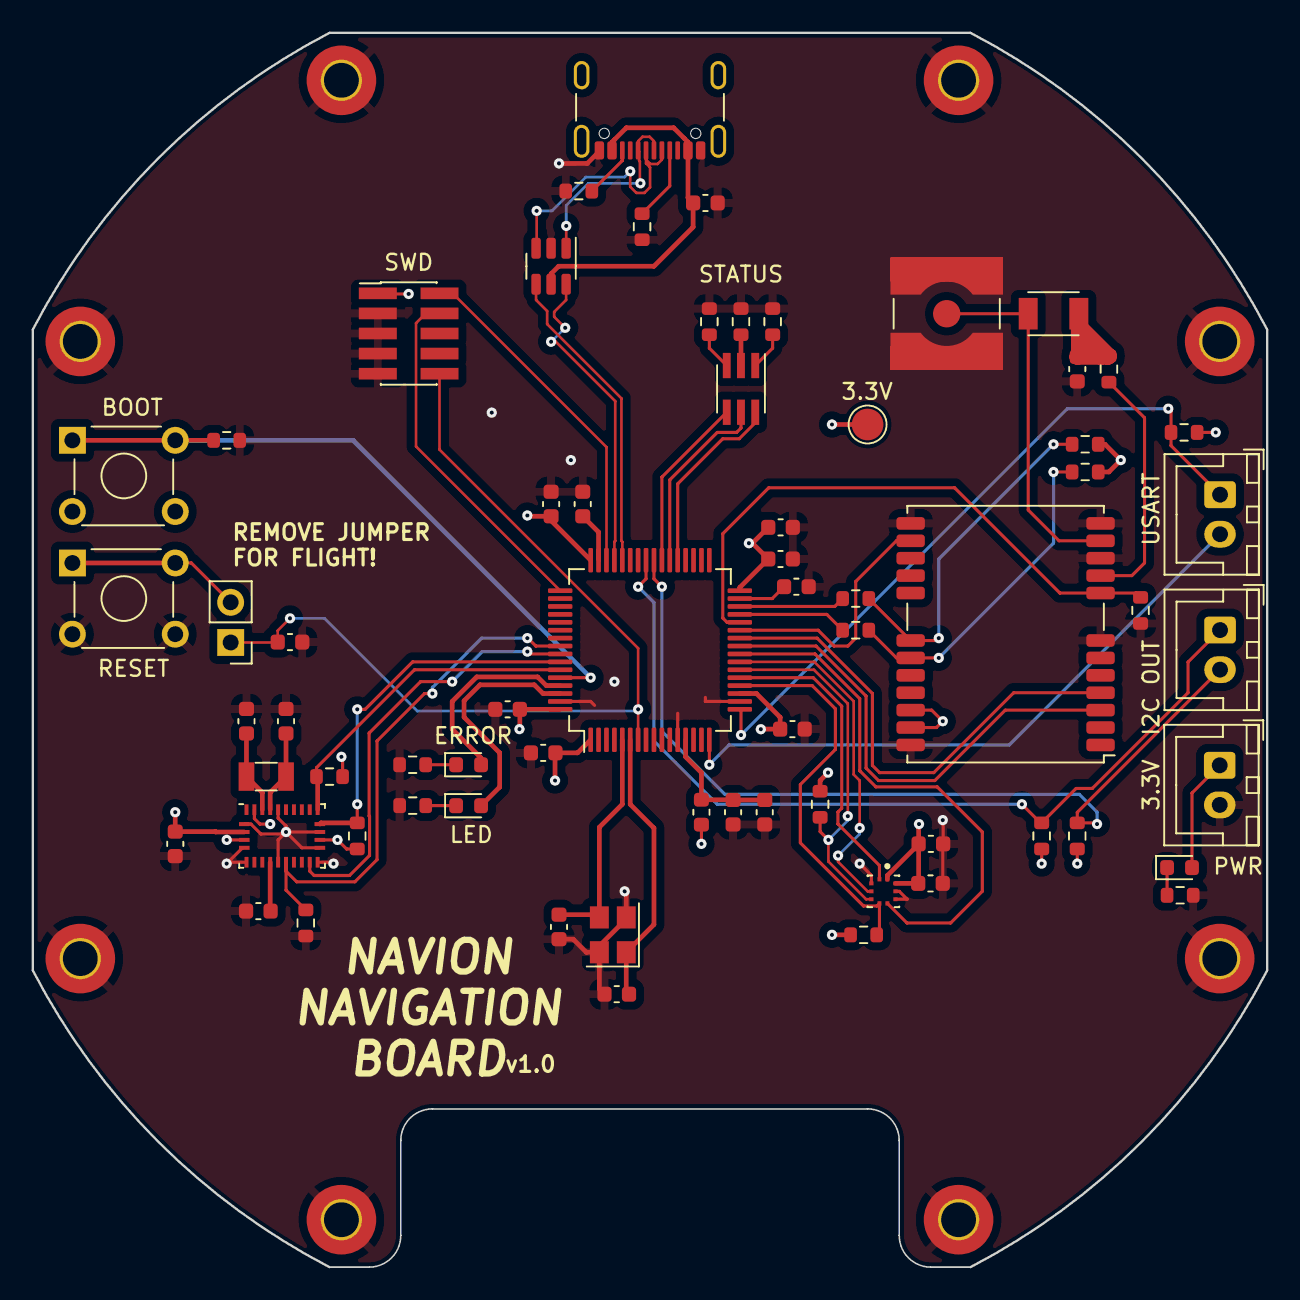
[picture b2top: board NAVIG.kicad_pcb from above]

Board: 4 copper layers, 78.0 x 78.0 mm, 75 parts (0 on the bottom side), 57 nets.

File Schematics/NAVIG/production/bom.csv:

Designator,Footprint,Quantity,Value,LCSC Part #
"C1, C10, C11, C12, C13, C14, C16, C2, C22, C3, C4, C7, C9",0603,13,100nF,
C15,0603,1,1uF,
"C19, C20, C5, C6",0603,4,22pF,
"C21, C23",0603,2,2.2uF,
C8,0603,1,4.7uF,
D1,LED_Avago_PLCC6_3x2.8mm,1,ASMT-YTB7-0AA02,
D2,0603,1,RED LED,
D3,0603,1,BLUE LED,
D4,0603,1,GREEN LED,
"H1, H2, H3, H4, H5, H6, H7, H8",MountingHole_2.2mm_M2_Pad_TopBottom,8,MountingHole_Pad,
J1,SMA_Amphenol_132134-10_Vertical,1,GNSS_SMA,
J2,PinHeader_2x05_P1.27mm_Vertical_SMD,1,SWD,
J3,JST_XH_B2B-XH-A_1x02_P2.50mm_Vertical,1,USART,
J4,JST_XH_B2B-XH-A_1x02_P2.50mm_Vertical,1,3.3V IN,
J5,JST_XH_B2B-XH-A_1x02_P2.50mm_Vertical,1,CNTRL I2C,
J6,USB_C_Receptacle_GCT_USB4105-xx-A_16P_TopMnt_Horizontal,1,USB_C_Receptacle_USB2.0,
J7,PinHeader_1x02_P2.54mm_Vertical,1,Reset Jumper,
L1,L_TDK_NLV32_3.2x2.5mm,1,27nH,
L2,0603,1,39nH,
"R1, R13, R2, R21, R7, R8",0603,6,4.7K,
"R10, R14, R22, R23, R9",0603,5,10K,
"R11, R12",0603,2,5.1K,
"R15, R16, R17, R18, R19, R20",0603,6,220R,
"R3, R4",0603,2,33R,
R5,0603,1,10R,
R6,0603,1,100K,
"SW1, SW2",SW_TH_Tactile_Omron_B3F-10xx,2,Omron_B3F-10xx,
TP1,TestPoint_Pad_D2.0mm,1,3.3V,
U1,XDCR_BMP390L,1,BMP390,
U2,LGA-28_5.2x3.8mm_P0.5mm,1,BNO055,
U3,ublox_NEO,1,NEO-M9N,
U4,LQFP-64_10x10mm_P0.5mm,1,STM32F205RETx,
U6,SOT-23-6,1,USBLC6-2SC6,
Y1,Crystal_SMD_3215-2Pin_3.2x1.5mm,1,32.768KHz,
Y2,Crystal_SMD_3225-4Pin_3.2x2.5mm,1,12MHz_ECS-120-18-33-JGN-TR3,
